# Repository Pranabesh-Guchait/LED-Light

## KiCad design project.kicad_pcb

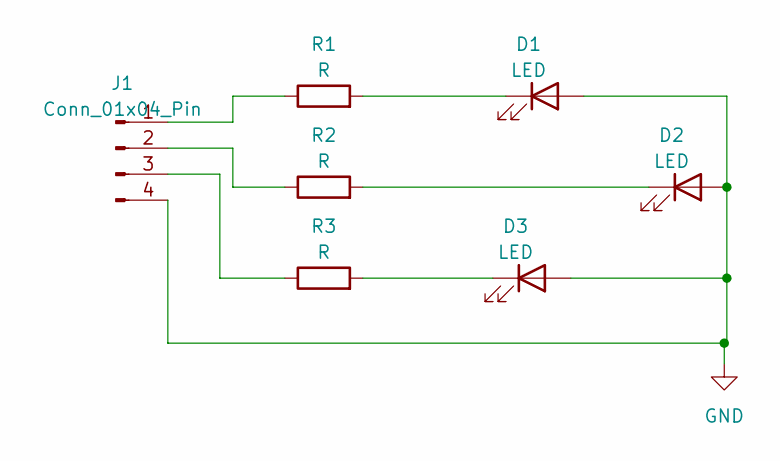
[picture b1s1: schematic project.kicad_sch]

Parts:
D1, D2, D3: LED; LED_D3.0mm
J1: Conn_01x04_Pin; PinHeader_1x04_P1.00mm_Vertical
R1, R2, R3: R; R_Axial_DIN0204_L3.6mm_D1.6mm_P5.08mm_Horizontal

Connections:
GND: D1.2 (A), D2.2 (A), D3.2 (A), J1.4
unnamed: D1.1 (K), R1.2
unnamed: D2.1 (K), R2.2
unnamed: D3.1 (K), R3.2
unnamed: J1.1, R1.1
unnamed: J1.2, R2.1
unnamed: J1.3, R3.1

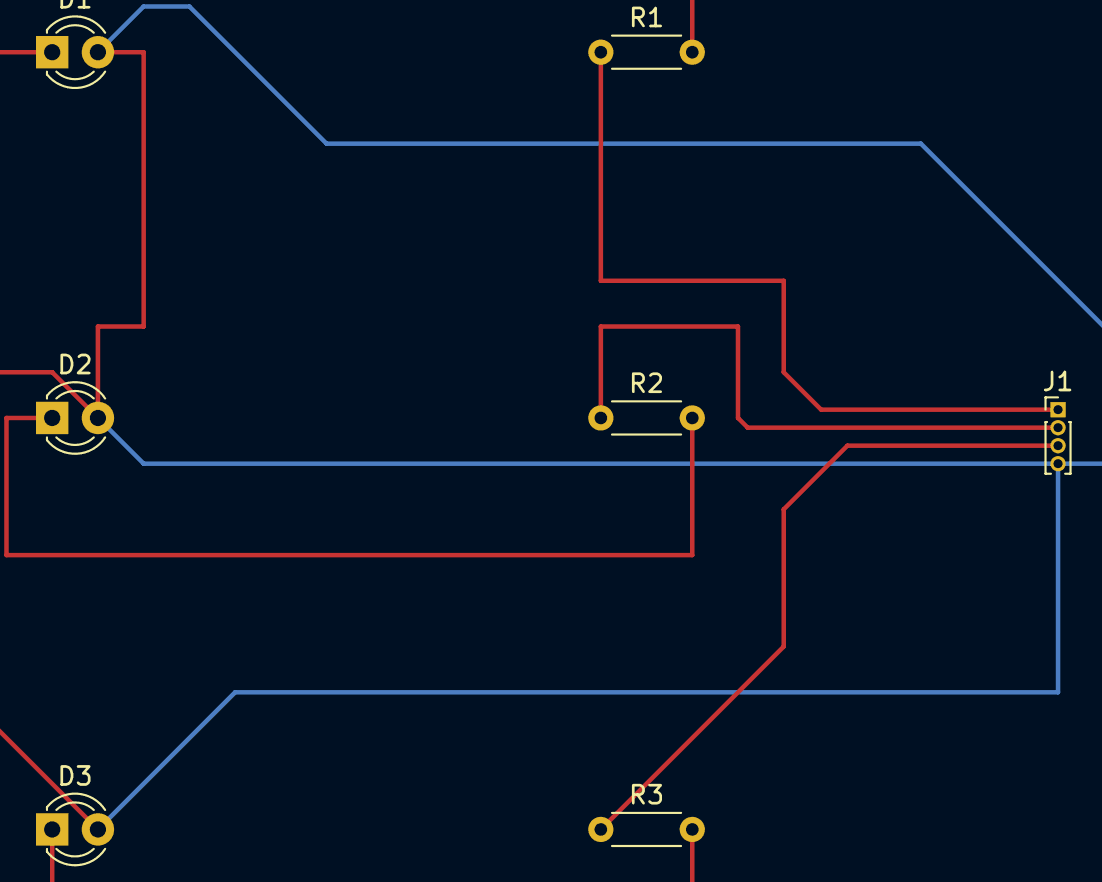
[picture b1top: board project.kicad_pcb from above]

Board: 2 copper layers, 7 parts (0 on the bottom side), 7 nets.
